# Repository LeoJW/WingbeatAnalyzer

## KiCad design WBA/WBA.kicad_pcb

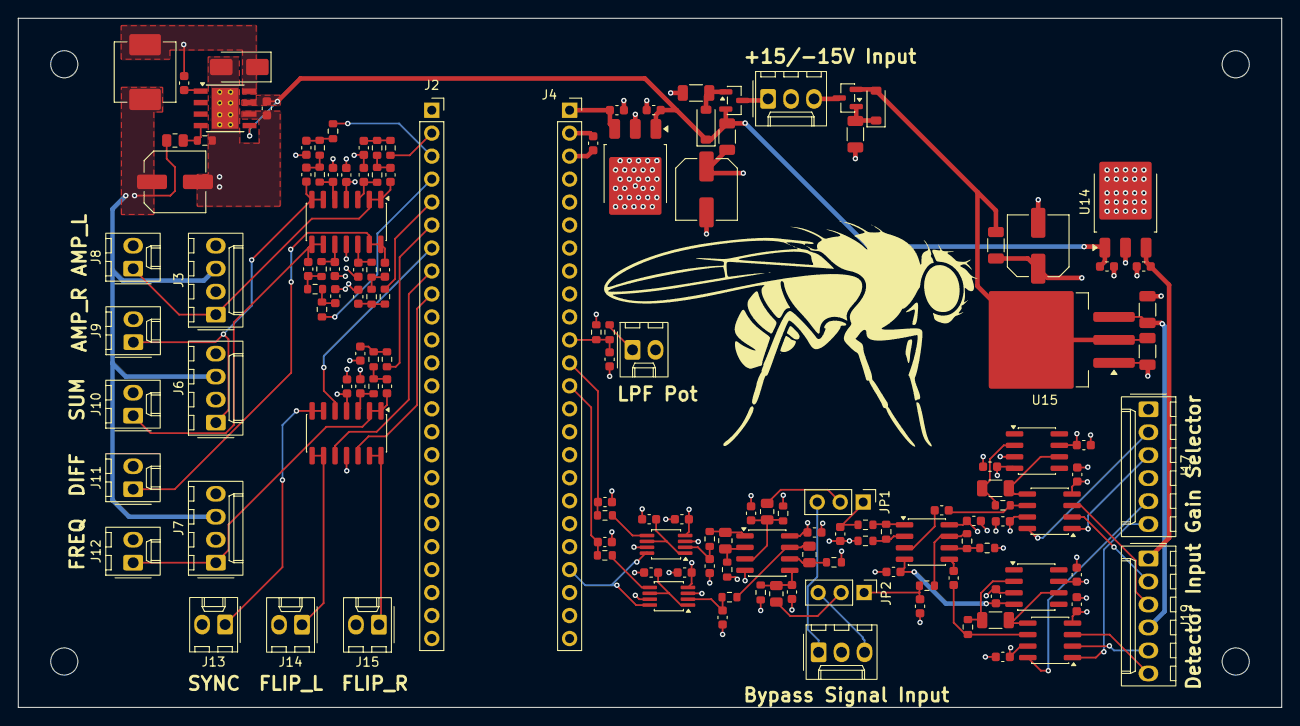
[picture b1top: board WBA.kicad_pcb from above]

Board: 4 copper layers, 139.7 x 76.2 mm, 140 parts (0 on the bottom side), 91 nets.

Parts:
C1, C3, C44, C45: 6.8nF; C_0603_1608Metric
C2, C4: 2.2nF; C_0603_1608Metric
C5, C6: 100uF; C_Elec_6.3x5.4
C7, C12, C15, C18, C21: 3.3nF; C_0603_1608Metric
C8, C11, C14, C17, C20, C61, C62: 1nF; C_0603_1608Metric
C9, C10, C13, C16, C19: 4.7nF; C_0603_1608Metric
C28, C54: 0.33uF; C_0603_1608Metric
C29, C38, C39, C40, C41, C42, C43, C46, C47, C58, C63, C64, C66, C67, C69, C70, C71, C72, C81: 0.1uF; C_0603_1608Metric
C30, C57: 10nF; C_0603_1608Metric
C31: 220uF; C_Elec_6.3x5.4
C52, C83: 10uF; C_0603_1608Metric
C59, C60: 20nF; C_0603_1608Metric
C65, C68: 100nF; C_1206_3216Metric
C73: 2.2uF; C_1206_3216Metric
C82: 1uF; C_1206_3216Metric
D1, D2: 1N4148W; D_SOD-123
D8: B340; D_SMA
J1: Signal input; Molex_KK-254_AE-6410-03A_1x03_P2.54mm_Vertical
J2, J4: Conn_01x24; PinSocket_1x24_P2.54mm_Vertical
J3, J6, J7: Conn_01x04; Molex_KK-254_AE-6410-04A_1x04_P2.54mm_Vertical
J5: Input Power; Molex_KK-254_AE-6410-03A_1x03_P2.54mm_Vertical
J8, J9, J10, J11, J12, J13, J14, J15: Conn_01x02; Molex_KK-254_AE-6410-02A_1x02_P2.54mm_Vertical
J16: LPF_potentiometer_100k; Molex_KK-254_AE-6410-02A_1x02_P2.54mm_Vertical
J17: Amp Selector; Molex_KK-254_AE-6410-06A_1x06_P2.54mm_Vertical
J19: Detector Input; Molex_KK-254_AE-6410-06A_1x06_P2.54mm_Vertical
JP1, JP2: Jumper_3_Open; PinHeader_1x03_P2.54mm_Vertical
L3: 15uH; L_Changjiang_FXL0630
Q1: A03400A; SOT-23
Q2: A03401A; SOT-23
R1, R5, R7, R33, R52: 10k; R_0805_2012Metric
R2, R4, R8, R9: 20k; R_0603_1608Metric
R3, R6, R10, R15, R18, R21, R24, R34, R35, R43, R44, R47, R48: 1k; R_0603_1608Metric
R11, R12, R13, R14, R16, R17, R19, R20, R22, R23: 5.6k; R_0603_1608Metric
R36, R38: 1M; R_1206_3216Metric
R40, R51: 22; R_1206_3216Metric
R41: 2.2k; R_0603_1608Metric
R42: 100k; R_0603_1608Metric
R45, R46: 47k; R_0603_1608Metric
R49, R50: 220k; R_0603_1608Metric
R53: 3.24k; R_0603_1608Metric
U2: TLV2372; SOIC-8_3.9x4.9mm_P1.27mm
U3, U4: MAX7414xUA; MSOP-8_3x3mm_P0.65mm
U8, U14: L7805; TO-252-3_TabPin2
U12: TL072; SOIC-8_3.9x4.9mm_P1.27mm
U15: L7905; TO-263-3_TabPin2
U16: TPS5430DDA; TI_SO-PowerPAD-8_ThermalVias
U19, U20: TLV2374IDR; SOIC-14_3.9x8.7mm_P1.27mm
U21, U22: OP07BRZ; SOIC-8_3.9x4.9mm_P1.27mm
U23, U24: INA128; SOIC-8_3.9x4.9mm_P1.27mm

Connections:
+3.3V: C39.1, C40.1, C43.1, C46.1, C47.1, C52.1, J4.3, R4.2, R9.2, R42.1, U2.8 (V+), U3.4 (V_{DD}), U3.7 (~SHDN), U4.4 (V_{DD}), U4.7 (~SHDN), U19.4 (V+), U20.4 (V+)
+5V: C29.1, J4.1, U8.3 (OUT)
+5V_{detector}: C81.1, J19.1, U14.3 (OUT)
+5V_{display}: C31.1, J3.3, J6.3, J7.3, L3.2, R52.1
+15V: C5.1, C38.1, C63.1, C66.1, C70.1, C72.1, R51.2, U12.8 (V+), U21.7 (V+), U22.7 (V+), U23.7 (V+), U24.7 (V+)
-5V_{detector}: C82.2, J19.4, U15.3 (VO)
-15V: C6.1, C58.1, C64.1, C67.1, C69.1, C71.1, R40.2, U12.4 (V-), U21.4 (V-), U22.4 (V-), U23.4 (V-), U24.4 (V-)
/AMP_L: J2.2, R10.2
/AMP_R: J2.3, R15.2
/DIFF: J2.5, R21.2
/FLIP_L: J2.8, U20.10 (+)
/FLIP_R: J2.9, U20.12 (+)
/FREQ: J2.6, R24.2
/Input_Amp/L: J19.3, U23.3 (+)
/Input_Amp/L AMP SEL 1: J17.2, U23.8 (Rg)
/Input_Amp/L AMP SEL 2: J17.3, U23.1 (Rg)
/Input_Amp/L REF: J19.2, U23.2 (-)
/Input_Amp/L_{signal}: JP1.2 (C), R5.1
/Input_Amp/R: J19.6, U24.3 (+)
/Input_Amp/R AMP SEL 1: J17.5, U24.8 (Rg)
/Input_Amp/R AMP SEL 2: J17.6, U24.1 (Rg)
/Input_Amp/R REF: J19.5, U24.2 (-)
/Input_Amp/R_{signal}: JP2.2 (C), R33.1
/L ADCin: C44.1, J4.12, R34.1
/LPF_pot: C57.1, J4.11, R41.1, R42.2
/R ADCin: C45.1, J4.13, R35.1
/SUM: J2.4, R18.2
/SYNC: J2.7, U20.5 (+)
GND: C1.2, C2.2, C3.2, C4.2, C5.2, C6.2, C7.2, C8.2, C11.2, C12.2, C14.2, C15.2, C17.2, C18.2, C20.2, C21.2, C28.2, C29.2, C31.2, C38.2, C39.2, C40.2, C41.2, C42.2, C43.2, C44.2, C45.2, C46.2, C47.2, C52.2, C54.2, C57.2, C58.2, C59.2, C60.2, C63.2, C64.2, C66.2, C67.2, C69.2, C70.2, C71.2, C72.2, C73.1, C81.2, C82.1, C83.2, D8.2 (A), J1.2, J2.1, J3.2, J3.4, J4.2, J5.2, J6.2, J6.4, J7.2, J7.4, J8.2, J9.2, J10.2, J11.2, J12.2, J13.2, J14.2, J15.2, J16.2, J17.1, J17.4, R2.1, R8.1, R36.2, R38.2, R47.1, R48.1, R53.2, U2.4 (V-), U3.3 (GND), U4.3 (GND), U8.2 (GND), U14.2 (GND), U15.1 (GND), U16.6 (GND), U16.9 (GNDPAD), U19.11 (V-), U20.11 (V-), U21.3 (+), U22.3 (+)
unnamed: C7.1, R10.1, R11.2
unnamed: C9.2, R11.1, R12.2
unnamed: C10.2, R13.2, R14.1
unnamed: C12.1, R14.2, R15.1
unnamed: C13.1, R16.2, R17.1
unnamed: C15.1, R17.2, R18.1
unnamed: C16.2, R19.2, R20.1
unnamed: C18.1, R20.2, R21.1
unnamed: C19.2, R22.2, R23.1
unnamed: C21.1, R23.2, R24.1
unnamed: C61.2, R49.2, U23.6
unnamed: C62.2, R50.2, U24.6
unnamed: D1.2 (A), Q2.1 (G), R36.1
unnamed: C28.1, C54.1, C83.1, D1.1 (K), Q2.2 (S), R51.1, U8.1 (IN), U14.1 (IN), U16.5 (EN), U16.7 (VIN)
unnamed: C73.2, D2.2 (A), Q1.2 (S), R40.1, U15.2 (VI)
unnamed: D2.1 (K), Q1.1 (G), R38.1
unnamed: C30.2, D8.1 (K), L3.1, U16.8 (PH)
unnamed: J1.1, JP1.3 (B)
unnamed: J1.3, JP2.3 (B)
unnamed: C9.1, J3.1, J8.1, U19.1, U19.2 (-)
unnamed: J4.21, U3.8 (CLK), U4.8 (CLK)
unnamed: J5.1, Q2.3 (D)
unnamed: J5.3, Q1.3 (D)
unnamed: C10.1, J6.1, J9.1, U19.6 (-), U19.7
unnamed: C13.2, J10.1, U19.8, U19.9 (-)
unnamed: C16.1, J11.1, U19.13 (-), U19.14
unnamed: C19.1, J7.1, J12.1, U20.1, U20.2 (-)
unnamed: J13.1, U20.6 (-), U20.7
unnamed: J14.1, U20.8, U20.9 (-)
unnamed: J15.1, U20.13 (-), U20.14
unnamed: J16.1, R41.2
unnamed: C59.1, JP1.1 (A), R43.1
unnamed: C60.1, JP2.1 (A), R44.1
unnamed: R1.1, R3.2, U2.1
unnamed: R6.2, R7.1, U2.7
unnamed: R43.2, R45.1, U12.1
unnamed: R44.2, R46.1, U12.7
unnamed: C2.1, R4.1, R5.2, U2.3 (+)
unnamed: R1.2, R2.2, U2.2 (-)
unnamed: C4.1, R9.1, R33.2, U2.5 (+)
unnamed: R7.2, R8.2, U2.6 (-)
unnamed: C42.1, U3.1 (COM), U3.6 (OS)
unnamed: C3.1, R6.1, U3.2 (IN)
unnamed: R35.2, U3.5 (OUT)
unnamed: C41.1, U4.1 (COM), U4.6 (OS)
unnamed: C1.1, R3.1, U4.2 (IN)
unnamed: R34.2, U4.5 (OUT)
unnamed: C61.1, U12.3 (+)
unnamed: R45.2, R47.2, U12.2 (-)
unnamed: C62.1, U12.5 (+)
unnamed: R46.2, R48.2, U12.6 (-)
unnamed: C30.1, U16.1 (BOOT)
unnamed: R52.2, R53.1, U16.4 (VSENSE)
unnamed: C8.1, R12.1, U19.3 (+)
unnamed: C11.1, R13.1, U19.5 (+)
unnamed: C14.1, R16.1, U19.10 (+)
unnamed: C17.1, R19.1, U19.12 (+)
unnamed: C20.1, R22.1, U20.3 (+)
unnamed: C65.2, R49.1, U21.2 (-)
unnamed: C68.2, R50.1, U22.2 (-)
unnamed: C65.1, U21.6, U23.5 (Ref)
unnamed: C68.1, U22.6, U24.5 (Ref)

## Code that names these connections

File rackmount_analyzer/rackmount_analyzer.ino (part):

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 *   Pin 6   Fundamental frequency of selected channel
 *
 * DIGITAL (TTL) OUTPUTS:
 *   Pin 7   SYNC   — one pulse per cycle of the selected channel
 *   Pin 8   L FLIP — one pulse per L cycle, timed to the waveform minimum
 *   Pin 9   R FLIP — one pulse per R cycle, timed to the waveform minimum
 *
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// ------------------------- Pin assignments -------------------------
constexpr uint8_t PIN_ADC_L    = A1;   // pin 15
constexpr uint8_t PIN_ADC_R    = A0;   // pin 14
constexpr uint8_t PIN_LPF_POT  = A2;   // pin 16
constexpr uint8_t PIN_SWITCH   = 10;

constexpr uint8_t PIN_OUT_AMP_L = 2;
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constexpr uint8_t PIN_OUT_DIFF  = 5;
constexpr uint8_t PIN_OUT_FREQ  = 6;

constexpr uint8_t PIN_SYNC    = 7;
constexpr uint8_t PIN_FLIP_L  = 8;
constexpr uint8_t PIN_FLIP_R  = 9;

constexpr uint8_t PIN_SCF_CLK = 36;

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      ch.freshCycle = true;

      if (isSelected) {
        digitalWriteFast(PIN_SYNC, HIGH);
        syncEndUs  = now + PULSE_US;
        syncActive = true;
      }
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  int32_t rawR = analogRead(PIN_ADC_R);

  bool selR = selectR;
  processSample(chL, rawL, now, !selR, PIN_FLIP_L);
  processSample(chR, rawR, now,  selR, PIN_FLIP_R);

  if (syncActive && (int32_t)(now - syncEndUs) >= 0) {
    syncActive = false;
    digitalWriteFast(PIN_SYNC, LOW);
  }

  // The pot MUST be sampled here, not in loop(). Teensyduino's analogRead is
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  static uint32_t potDecim = 0;
  if (++potDecim >= 2500) {
    potDecim = 0;
    potRaw = analogRead(PIN_LPF_POT);
  }
}

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  pinMode(PIN_SCF_CLK, OUTPUT);
  applyCutoff(1.0f);                 // default to widest cutoff

  pinMode(PIN_SYNC,   OUTPUT);  digitalWriteFast(PIN_SYNC,   LOW);
  pinMode(PIN_FLIP_L, OUTPUT);  digitalWriteFast(PIN_FLIP_L, LOW);
  pinMode(PIN_FLIP_R, OUTPUT);  digitalWriteFast(PIN_FLIP_R, LOW);

  pinMode(PIN_SWITCH, INPUT_PULLUP);
  selectR = (digitalRead(PIN_SWITCH) == LOW);
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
